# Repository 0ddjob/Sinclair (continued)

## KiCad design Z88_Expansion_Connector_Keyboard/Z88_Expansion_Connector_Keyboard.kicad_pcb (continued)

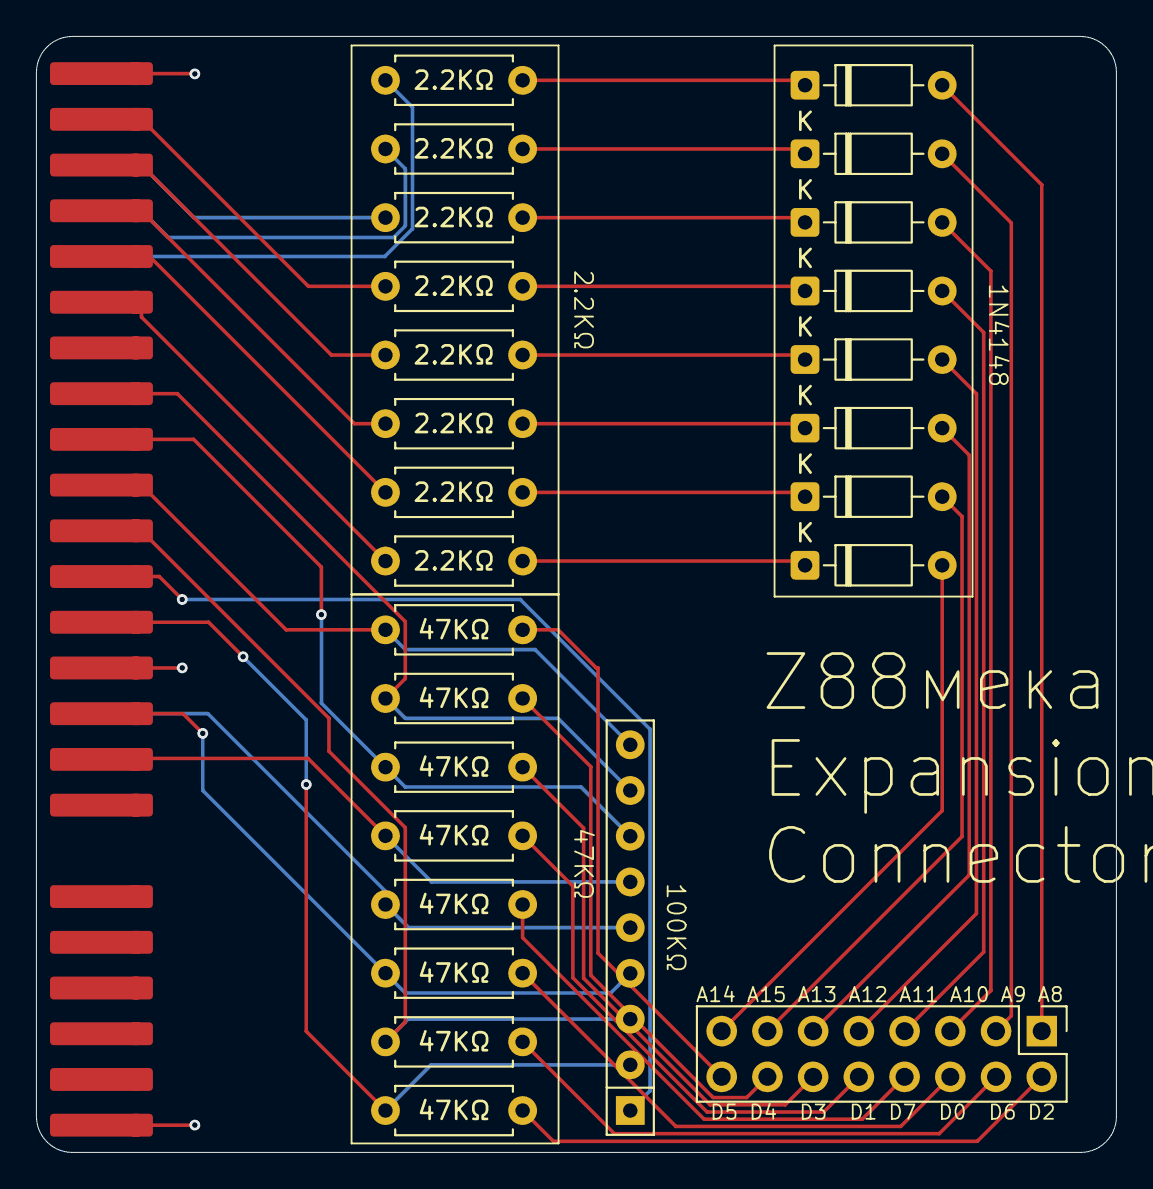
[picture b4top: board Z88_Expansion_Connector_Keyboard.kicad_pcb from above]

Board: 2 copper layers, 60.0 x 62.0 mm, 27 parts (0 on the bottom side), 42 nets.

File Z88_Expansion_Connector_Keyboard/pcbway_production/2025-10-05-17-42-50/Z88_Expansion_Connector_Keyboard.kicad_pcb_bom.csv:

Designator,Quantity,Value,Footprint,Package,MPN,DNP,Mount_Type,Description,Sim.Device,Sim.Pins
"D1, D2, D3, D4, D5, D6, D7, D8",8,1N4148,D_DO-35_SOD27_P7.62mm_Horizontal,,,,tht,"100V 0.15A standard switching diode, DO-35",D,1=K 2=A
J1,1,Z88 Expansion Connector,Z88 Expansion Connector,,,,tht,Z88 Cambridge Computer expansion connector,,
J2,1,From Keyboard,PinHeader_2x08_P2.54mm_Vertical,,,,tht,"Generic connector, double row, 02x08, odd/even pin numbering scheme (row 1 odd numbers, row 2 even numbers), script generated (kicad-library-utils/schlib/autogen/connector/)",,
"R1, R2, R3, R4, R5, R6, R7, R8",8,2.2KΩ,R_Axial_DIN0207_L6.3mm_D2.5mm_P7.62mm_Horizontal,,,,tht,Resistor,,
"R10, R11, R12, R13, R14, R15, R16, R9",8,47KΩ,R_Axial_DIN0207_L6.3mm_D2.5mm_P7.62mm_Horizontal,,,,tht,Resistor,,
RN1,1,100KΩ,R_Array_SIP9,,,,tht,"8 resistor network, star topology, bussed resistors, small symbol",,

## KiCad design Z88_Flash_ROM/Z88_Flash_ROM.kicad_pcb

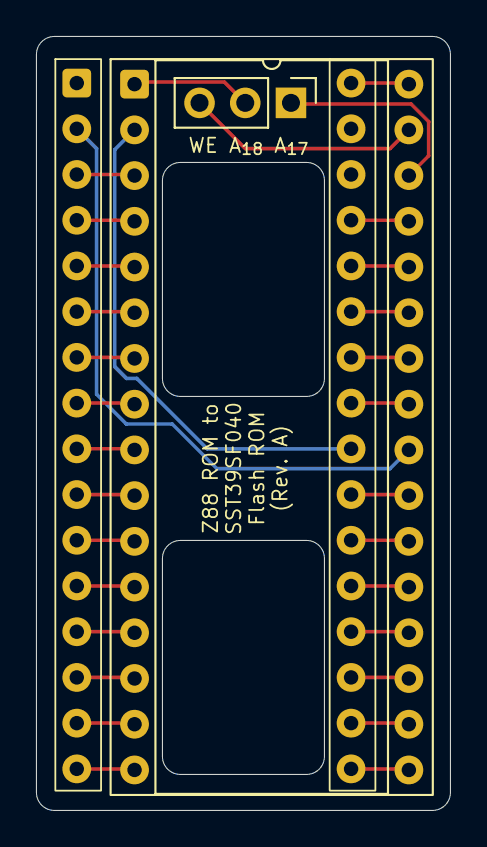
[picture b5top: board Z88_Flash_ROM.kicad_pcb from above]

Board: 2 copper layers, 23.0 x 43.0 mm, 3 parts (0 on the bottom side), 32 nets.

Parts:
J1: Conn_01x03; PinHeader_1x03_P2.54mm_Vertical
U1: SST39SF040; DIP-32_W15.24mm_Socket
U2: Z88_ROM; DIP-32_Adapter

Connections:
+5V: U1.32 (VCC), U2.32 (VCC)
/A_{0}: U1.12 (A0), U2.12 (A_{0})
/A_{1}: U1.11 (A1), U2.11 (A_{1})
/A_{2}: U1.10 (A2), U2.10 (A_{2})
/A_{3}: U1.9 (A3), U2.9 (A_{3})
/A_{4}: U1.8 (A4), U2.8 (A_{4})
/A_{5}: U1.7 (A5), U2.7 (A_{5})
/A_{6}: U1.6 (A6), U2.6 (A_{6})
/A_{7}: U1.5 (A7), U2.5 (A_{7})
/A_{8}: U1.27 (A8), U2.27 (A_{8})
/A_{9}: U1.26 (A9), U2.26 (A_{9})
/A_{10}: U1.23 (A10), U2.23 (A_{10})
/A_{11}: U1.25 (A11), U2.25 (A_{11})
/A_{12}: U1.4 (A12), U2.4 (A_{12})
/A_{13}: U1.28 (A13), U2.28 (A_{13})
/A_{14}: U1.29 (A14), U2.29 (A_{14})
/A_{15}: U1.3 (A15), U2.3 (A_{15})
/A_{16}: U1.2 (A16), U2.24 (A_{16})
/CE: U1.22 (CE), U2.22 (IPCE)
/D_{0}: U1.13 (D0), U2.13 (D_{0})
/D_{1}: U1.14 (D1), U2.14 (D_{1})
/D_{2}: U1.15 (D2), U2.15 (D_{2})
/D_{3}: U1.17 (D3), U2.17 (D_{3})
/D_{4}: U1.18 (D4), U2.18 (D_{4})
/D_{5}: U1.19 (D5), U2.19 (D_{5})
/D_{6}: U1.20 (D6), U2.20 (D_{6})
/D_{7}: U1.21 (D7), U2.21 (D_{7})
/ROE: U1.24 (OE), U2.2 (ROE)
A_{17}: J1.1, U1.30 (A17)
A_{18}: J1.2, U1.1 (A18)
GND: U1.16 (GND), U2.16 (GND)
WE: J1.3, U1.31 (PGM)

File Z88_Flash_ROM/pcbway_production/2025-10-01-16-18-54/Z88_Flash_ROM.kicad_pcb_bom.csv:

Designator,Quantity,Value,Footprint,Package,MPN,DNP,Mount_Type,Description
J1,1,Conn_01x03,PinHeader_1x03_P2.54mm_Vertical,,,,tht,"Generic connector, single row, 01x03, script generated (kicad-library-utils/schlib/autogen/connector/)"
U1,1,SST39SF040,DIP-32_W15.24mm_Socket,,,,tht,Silicon Storage Technology (SSF) 512k x 8 Flash ROM
U2,1,Z88_ROM,DIP-32_Adapter,,,,tht,

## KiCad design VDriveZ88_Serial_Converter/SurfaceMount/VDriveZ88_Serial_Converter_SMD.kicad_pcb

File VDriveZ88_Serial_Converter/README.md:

# VDrive Serial Interface Converter for Z88
Refer to [Ben Vyre's project page](https://benryves.com/products/vdrivez88) and [Github](https://github.com/benryves/VDriveZ88/) for the background.

## RS232 Serial Pinouts
Note that this design uses the Z88's non-standard DE9 RS232 pin numbering.<br>
For [standard RS232 pin numbering](https://cambridgez88.jira.com/wiki/spaces/UG/pages/35913795/Appendix+B+-+Serial+port+and+transfer+protocols):<br>
|Standard DE9|Z88 DE9|
|------------|-------|
| DCD (pin 1) | pin 8         |
| RXD (pin 2) | pin 3         |
| TXD (pin 3) | pin 2         |
| DTR (pin 4) | not connected |
| GND (pin 5) | pin 7         |
| DSR (pin 6) | pin 8         |
| RTS (pin 7) | pin 4         |
| CTS (pin 8) | pin 5         |
| RI  (pin 9) | not connected |

## BOM
- 1 x MAX232
- 1 x 2.2KΩ pullup resistor
- 5 x 1µF ceramic capacitors (2.5mm pitch)
- 1 x 9-way 2.54mm pitch pin header for Z88 serial
- 1 x 8-way 2mm pitch pin header for VDrive interface
- 1 x 2-way 2.54mm pin header for +5VDC power input
- 2 x M2 screws for mounting the PCB

Note that pin headers are optional - you could just directly solder the wires to the PCB.<br>

The centre of each M2 mounting hole is inset 3mm from each edge.<br>

## Status
9-Aug-2025: This design is currently untested

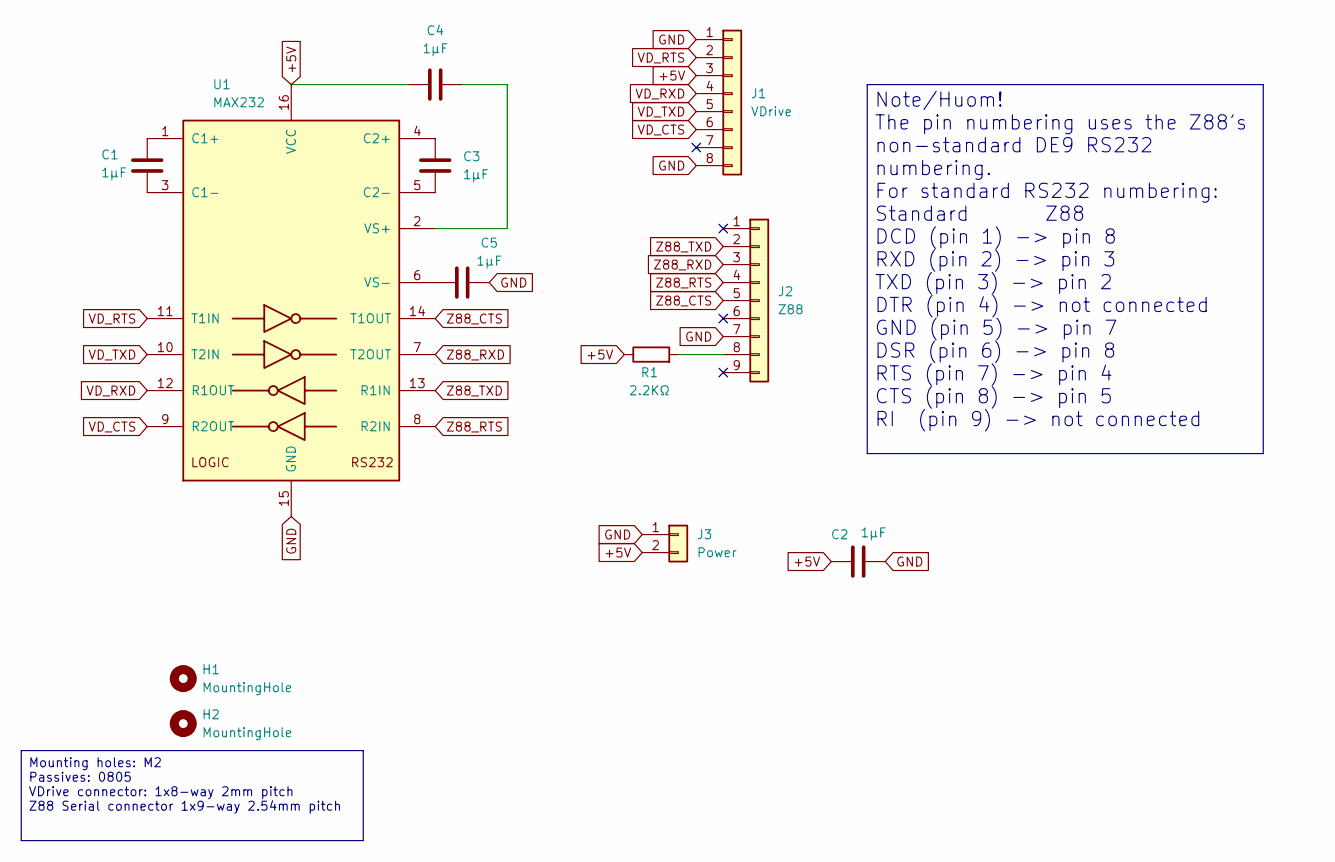
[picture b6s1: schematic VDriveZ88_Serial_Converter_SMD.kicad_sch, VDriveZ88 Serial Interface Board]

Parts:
C1, C2, C3, C4, C5: 1µF; C_0805_2012Metric_Pad1.18x1.45mm_HandSolder
H1, H2: MountingHole; MountingHole_2.2mm_M2
J1: VDrive; PinHeader_1x08_P2.00mm_Vertical
J2: Z88; PinHeader_1x09_P2.54mm_Vertical
J3: Power; PinHeader_1x02_P2.54mm_Vertical
R1: 2.2KΩ; R_0805_2012Metric_Pad1.20x1.40mm_HandSolder
U1: MAX232; SOIC-16W_7.5x10.3mm_P1.27mm

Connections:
+5V: C2.1, C4.1, J1.3, J3.2, R1.1, U1.16 (VCC)
GND: C2.2, C5.2, J1.1, J1.8, J2.7, J3.1, U1.15 (GND)
unnamed: J2.8, R1.2
unnamed: C1.1, U1.1 (C1+)
unnamed: C1.2, U1.3 (C1-)
unnamed: C3.1, U1.4 (C2+)
unnamed: C3.2, U1.5 (C2-)
unnamed: C4.2, U1.2 (VS+)
unnamed: C5.1, U1.6 (VS-)
VD_CTS: J1.6, U1.9 (R2OUT)
VD_RTS: J1.2, U1.11 (T1IN)
VD_RXD: J1.4, U1.12 (R1OUT)
VD_TXD: J1.5, U1.10 (T2IN)
Z88_CTS: J2.5, U1.14 (T1OUT)
Z88_RTS: J2.4, U1.8 (R2IN)
Z88_RXD: J2.3, U1.7 (T2OUT)
Z88_TXD: J2.2, U1.13 (R1IN)

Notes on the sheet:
Mounting holes: M2 Passives: 0805 VDrive connector: 1x8-way 2mm pitch Z88 Serial connector 1x9-way 2.54mm pitch
Note/Huom! The pin numbering uses the Z88's non-standard DE9 RS232 numbering. For standard RS232 numbering: Standard Z88 DCD (pin 1) -> pin 8 RXD (pin 2) -> pin 3 TXD (pin 3) -> pin 2 DTR (pin 4) -> not connected GND (pin 5) -> pin 7 DSR (pin 6) -> pin 8 RTS (pin 7) -> pin 4 CTS (pin 8) -> pin 5 RI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

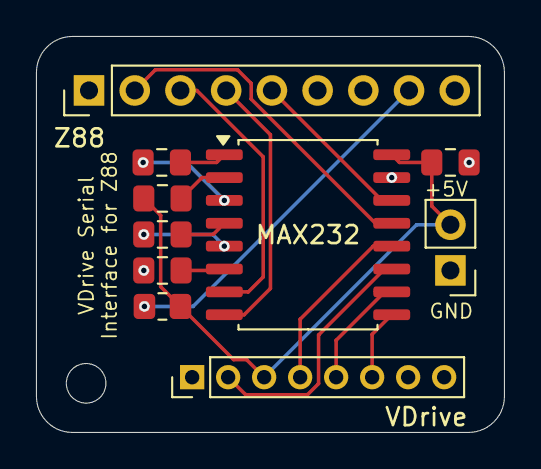
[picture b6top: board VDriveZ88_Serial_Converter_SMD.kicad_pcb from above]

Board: 2 copper layers, 26.0 x 22.0 mm, 11 parts (0 on the bottom side), 17 nets.

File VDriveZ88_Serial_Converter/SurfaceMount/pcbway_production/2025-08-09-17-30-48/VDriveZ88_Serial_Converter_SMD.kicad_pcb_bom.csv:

Designator,Quantity,Value,Footprint,Package,MPN,DNP,Mount_Type,Description
"C1, C2, C3, C4, C5",5,1µF,C_0805_2012Metric_Pad1.18x1.45mm_HandSolder,,,,smt,Unpolarized capacitor
J1,1,VDrive,PinHeader_1x08_P2.00mm_Vertical,,,,tht,"Generic connector, single row, 01x08, script generated (kicad-library-utils/schlib/autogen/connector/)"
J2,1,Z88,PinHeader_1x09_P2.54mm_Vertical,,,,tht,"Generic connector, single row, 01x09, script generated (kicad-library-utils/schlib/autogen/connector/)"
J3,1,Power,PinHeader_1x02_P2.54mm_Vertical,,,,tht,"Generic connector, single row, 01x02, script generated (kicad-library-utils/schlib/autogen/connector/)"
R1,1,2.2KΩ,R_0805_2012Metric_Pad1.20x1.40mm_HandSolder,,,,smt,Resistor
U1,1,MAX232,SOIC-16W_7.5x10.3mm_P1.27mm,,,,smt,"Dual RS232 driver/receiver, 5V supply, 120kb/s, 0C-70C"

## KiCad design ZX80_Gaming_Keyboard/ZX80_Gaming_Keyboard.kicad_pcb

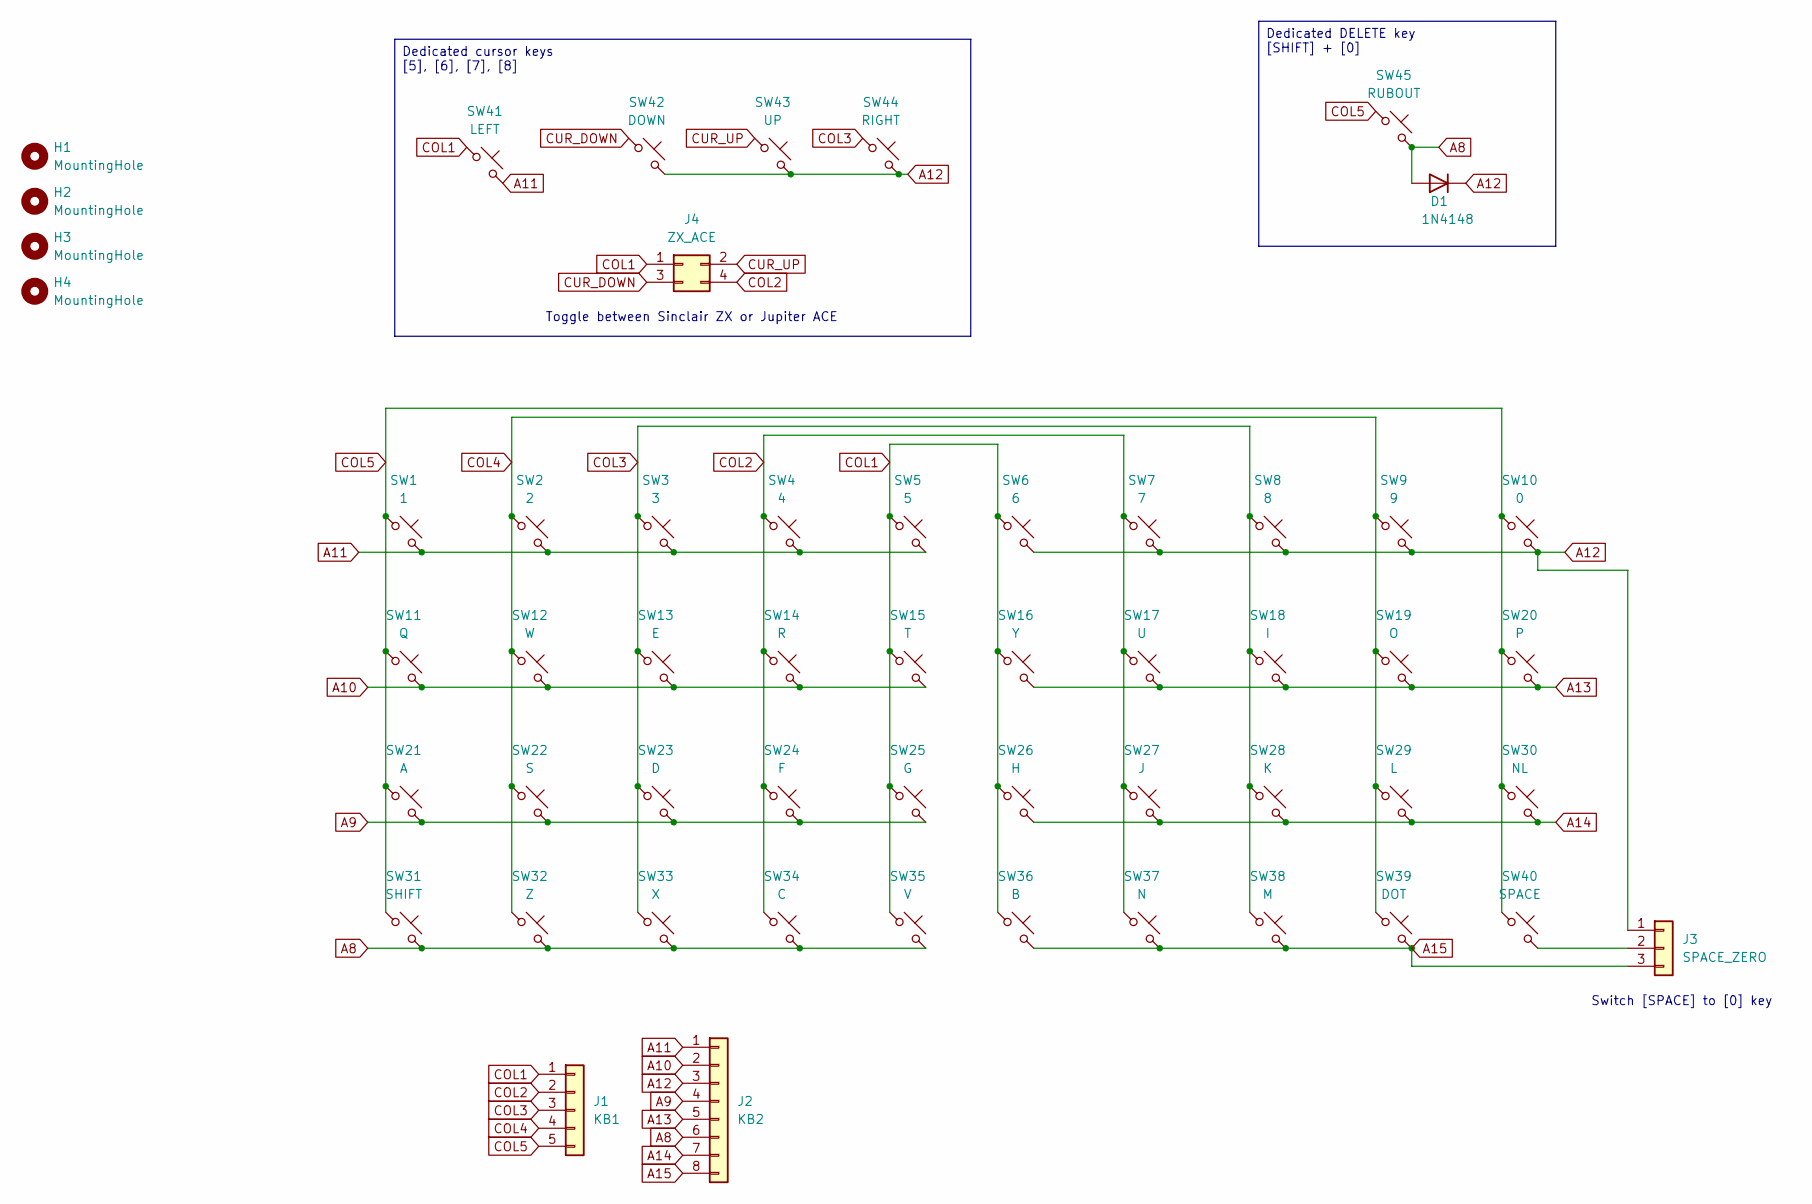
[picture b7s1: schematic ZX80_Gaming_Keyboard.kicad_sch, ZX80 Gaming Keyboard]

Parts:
D1: 1N4148; D_DO-35_SOD27_P7.62mm_Horizontal
H1, H2, H3, H4: MountingHole; MountingHole_3.2mm_M3
J1: KB1; PinHeader_1x05_P2.54mm_Vertical
J2: KB2; PinHeader_1x08_P2.54mm_Vertical
J3: SPACE_ZERO; PinHeader_1x03_P2.54mm_Vertical
J4: ZX_ACE; PinHeader_2x02_P2.54mm_Vertical
SW1: 1; SW_Cherry_MX_1.00u_PCB
SW2: 2; SW_Cherry_MX_1.00u_PCB
SW3: 3; SW_Cherry_MX_1.00u_PCB
SW4: 4; SW_Cherry_MX_1.00u_PCB
SW5: 5; SW_Cherry_MX_1.00u_PCB
SW6: 6; SW_Cherry_MX_1.00u_PCB
SW7: 7; SW_Cherry_MX_1.00u_PCB
SW8: 8; SW_Cherry_MX_1.00u_PCB
SW9: 9; SW_Cherry_MX_1.00u_PCB
SW10: 0; SW_Cherry_MX_1.00u_PCB
SW11: Q; SW_Cherry_MX_1.00u_PCB
SW12: W; SW_Cherry_MX_1.00u_PCB
SW13: E; SW_Cherry_MX_1.00u_PCB
SW14: R; SW_Cherry_MX_1.00u_PCB
SW15: T; SW_Cherry_MX_1.00u_PCB
SW16: Y; SW_Cherry_MX_1.00u_PCB
SW17: U; SW_Cherry_MX_1.00u_PCB
SW18: I; SW_Cherry_MX_1.00u_PCB
SW19: O; SW_Cherry_MX_1.00u_PCB
SW20: P; SW_Cherry_MX_1.00u_PCB
SW21: A; SW_Cherry_MX_1.00u_PCB
SW22: S; SW_Cherry_MX_1.00u_PCB
SW23: D; SW_Cherry_MX_1.00u_PCB
SW24: F; SW_Cherry_MX_1.00u_PCB
SW25: G; SW_Cherry_MX_1.00u_PCB
SW26: H; SW_Cherry_MX_1.00u_PCB
SW27: J; SW_Cherry_MX_1.00u_PCB
SW28: K; SW_Cherry_MX_1.00u_PCB
SW29: L; SW_Cherry_MX_1.00u_PCB
SW30: NL; SW_Cherry_MX_1.00u_PCB
SW31: SHIFT; SW_Cherry_MX_1.00u_PCB
SW32: Z; SW_Cherry_MX_1.00u_PCB
SW33: X; SW_Cherry_MX_1.00u_PCB
SW34: C; SW_Cherry_MX_1.00u_PCB
SW35: V; SW_Cherry_MX_1.00u_PCB
SW36: B; SW_Cherry_MX_1.00u_PCB
SW37: N; SW_Cherry_MX_1.00u_PCB
SW38: M; SW_Cherry_MX_1.00u_PCB
SW39: DOT; SW_Cherry_MX_1.00u_PCB
SW40: SPACE; SW_Cherry_MX_1.00u_PCB
SW41: LEFT; SW_Cherry_MX_1.00u_PCB
SW42: DOWN; SW_Cherry_MX_1.00u_PCB
SW43: UP; SW_Cherry_MX_1.00u_PCB
SW44: RIGHT; SW_Cherry_MX_1.00u_PCB
SW45: RUBOUT; SW_Cherry_MX_1.00u_PCB

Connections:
A8: D1.2 (A), J2.6, SW31.2, SW32.2, SW33.2, SW34.2, SW35.2, SW45.2
A9: J2.4, SW21.2, SW22.2, SW23.2, SW24.2, SW25.2
A10: J2.2, SW11.2, SW12.2, SW13.2, SW14.2, SW15.2
A11: J2.1, SW1.2, SW2.2, SW3.2, SW4.2, SW5.2, SW41.2
A12: D1.1 (K), J2.3, J3.1, SW6.2, SW7.2, SW8.2, SW9.2, SW10.2, SW42.2, SW43.2, SW44.2
A13: J2.5, SW16.2, SW17.2, SW18.2, SW19.2, SW20.2
A14: J2.7, SW26.2, SW27.2, SW28.2, SW29.2, SW30.2
A15: J2.8, J3.3, SW36.2, SW37.2, SW38.2, SW39.2
COL1: J1.1, J4.1, SW5.1, SW6.1, SW15.1, SW16.1, SW25.1, SW26.1, SW35.1, SW36.1, SW41.1
COL2: J1.2, J4.4, SW4.1, SW7.1, SW14.1, SW17.1, SW24.1, SW27.1, SW34.1, SW37.1
COL3: J1.3, SW3.1, SW8.1, SW13.1, SW18.1, SW23.1, SW28.1, SW33.1, SW38.1, SW44.1
COL4: J1.4, SW2.1, SW9.1, SW12.1, SW19.1, SW22.1, SW29.1, SW32.1, SW39.1
COL5: J1.5, SW1.1, SW10.1, SW11.1, SW20.1, SW21.1, SW30.1, SW31.1, SW40.1, SW45.1
CUR_DOWN: J4.3, SW42.1
CUR_UP: J4.2, SW43.1
unnamed: J3.2, SW40.2

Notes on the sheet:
Toggle between Sinclair ZX or Jupiter ACE
Switch [SPACE] to [0] key
Dedicated DELETE key [SHIFT] + [0]
Dedicated cursor keys [5], [6], [7], [8]

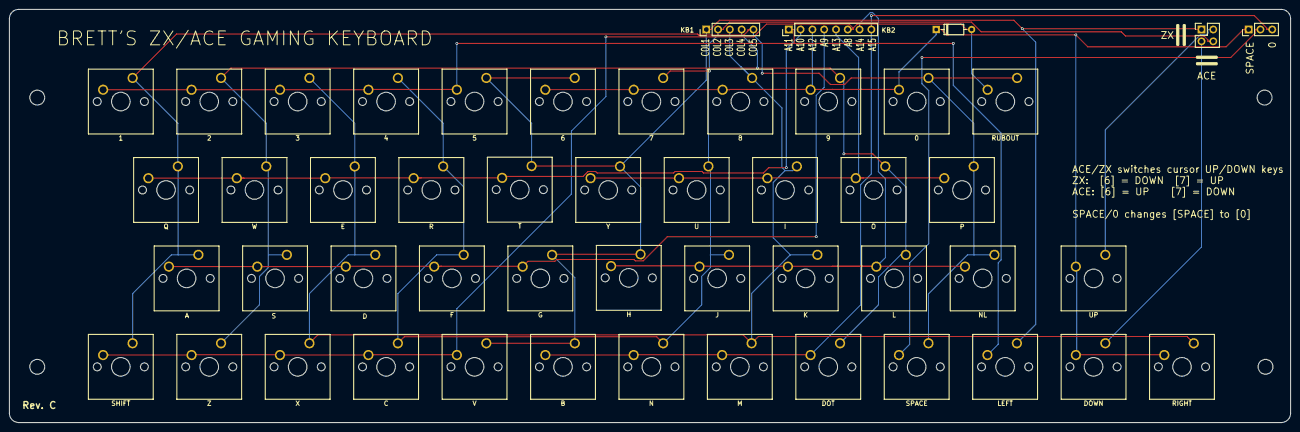
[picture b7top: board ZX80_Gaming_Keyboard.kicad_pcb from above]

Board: 2 copper layers, 276.0 x 89.0 mm, 54 parts (0 on the bottom side), 16 nets.

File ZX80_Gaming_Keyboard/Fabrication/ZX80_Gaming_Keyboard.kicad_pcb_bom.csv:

Designator,Quantity,Value,Footprint,Package,MPN,DNP,Mount_Type,Description,Sim.Device,Sim.Pins
"D1, D2",2,1N4148,D_DO-35_SOD27_P7.62mm_Horizontal,,,,tht,Diode,D,1=K 2=A
J1,1,KB1,PinHeader_1x05_P2.54mm_Vertical,,,,tht,"Generic connector, single row, 01x05, script generated (kicad-library-utils/schlib/autogen/connector/)",,
J2,1,KB2,PinHeader_1x08_P2.54mm_Vertical,,,,tht,"Generic connector, single row, 01x08, script generated (kicad-library-utils/schlib/autogen/connector/)",,
J3,1,SPACE_ZERO,PinHeader_1x03_P2.54mm_Vertical,,,,tht,"Generic connector, single row, 01x03, script generated (kicad-library-utils/schlib/autogen/connector/)",,
J4,1,ZX_ACE,PinHeader_2x02_P2.54mm_Vertical,,,,tht,"Generic connector, double row, 02x02, odd/even pin numbering scheme (row 1 odd numbers, row 2 even numbers), script generated (kicad-library-utils/schlib/autogen/connector/)",,
SW1,1,1,SW_Cherry_MX_1.00u_PCB,,,,tht,"Push button switch, normally open, two pins, 45° tilted",,
SW10,1,0,SW_Cherry_MX_1.00u_PCB,,,,tht,"Push button switch, normally open, two pins, 45° tilted",,
SW11,1,Q,SW_Cherry_MX_1.00u_PCB,,,,tht,"Push button switch, normally open, two pins, 45° tilted",,
SW12,1,W,SW_Cherry_MX_1.00u_PCB,,,,tht,"Push button switch, normally open, two pins, 45° tilted",,
SW13,1,E,SW_Cherry_MX_1.00u_PCB,,,,tht,"Push button switch, normally open, two pins, 45° tilted",,
SW14,1,R,SW_Cherry_MX_1.00u_PCB,,,,tht,"Push button switch, normally open, two pins, 45° tilted",,
SW15,1,T,SW_Cherry_MX_1.00u_PCB,,,,tht,"Push button switch, normally open, two pins, 45° tilted",,
SW16,1,Y,SW_Cherry_MX_1.00u_PCB,,,,tht,"Push button switch, normally open, two pins, 45° tilted",,
SW17,1,U,SW_Cherry_MX_1.00u_PCB,,,,tht,"Push button switch, normally open, two pins, 45° tilted",,
SW18,1,I,SW_Cherry_MX_1.00u_PCB,,,,tht,"Push button switch, normally open, two pins, 45° tilted",,
SW19,1,O,SW_Cherry_MX_1.00u_PCB,,,,tht,"Push button switch, normally open, two pins, 45° tilted",,
SW2,1,2,SW_Cherry_MX_1.00u_PCB,,,,tht,"Push button switch, normally open, two pins, 45° tilted",,
SW20,1,P,SW_Cherry_MX_1.00u_PCB,,,,tht,"Push button switch, normally open, two pins, 45° tilted",,
SW21,1,A,SW_Cherry_MX_1.00u_PCB,,,,tht,"Push button switch, normally open, two pins, 45° tilted",,
SW22,1,S,SW_Cherry_MX_1.00u_PCB,,,,tht,"Push button switch, normally open, two pins, 45° tilted",,
SW23,1,D,SW_Cherry_MX_1.00u_PCB,,,,tht,"Push button switch, normally open, two pins, 45° tilted",,
SW24,1,F,SW_Cherry_MX_1.00u_PCB,,,,tht,"Push button switch, normally open, two pins, 45° tilted",,
SW25,1,G,SW_Cherry_MX_1.00u_PCB,,,,tht,"Push button switch, normally open, two pins, 45° tilted",,
SW26,1,H,SW_Cherry_MX_1.00u_PCB,,,,tht,"Push button switch, normally open, two pins, 45° tilted",,
SW27,1,J,SW_Cherry_MX_1.00u_PCB,,,,tht,"Push button switch, normally open, two pins, 45° tilted",,
SW28,1,K,SW_Cherry_MX_1.00u_PCB,,,,tht,"Push button switch, normally open, two pins, 45° tilted",,
SW29,1,L,SW_Cherry_MX_1.00u_PCB,,,,tht,"Push button switch, normally open, two pins, 45° tilted",,
SW3,1,3,SW_Cherry_MX_1.00u_PCB,,,,tht,"Push button switch, normally open, two pins, 45° tilted",,
SW30,1,NL,SW_Cherry_MX_1.00u_PCB,,,,tht,"Push button switch, normally open, two pins, 45° tilted",,
SW31,1,SHIFT,SW_Cherry_MX_1.00u_PCB,,,,tht,"Push button switch, normally open, two pins, 45° tilted",,
SW32,1,Z,SW_Cherry_MX_1.00u_PCB,,,,tht,"Push button switch, normally open, two pins, 45° tilted",,
SW33,1,X,SW_Cherry_MX_1.00u_PCB,,,,tht,"Push button switch, normally open, two pins, 45° tilted",,
SW34,1,C,SW_Cherry_MX_1.00u_PCB,,,,tht,"Push button switch, normally open, two pins, 45° tilted",,
SW35,1,V,SW_Cherry_MX_1.00u_PCB,,,,tht,"Push button switch, normally open, two pins, 45° tilted",,
SW36,1,B,SW_Cherry_MX_1.00u_PCB,,,,tht,"Push button switch, normally open, two pins, 45° tilted",,
SW37,1,N,SW_Cherry_MX_1.00u_PCB,,,,tht,"Push button switch, normally open, two pins, 45° tilted",,
SW38,1,M,SW_Cherry_MX_1.00u_PCB,,,,tht,"Push button switch, normally open, two pins, 45° tilted",,
SW39,1,DOT,SW_Cherry_MX_1.00u_PCB,,,,tht,"Push button switch, normally open, two pins, 45° tilted",,
SW4,1,4,SW_Cherry_MX_1.00u_PCB,,,,tht,"Push button switch, normally open, two pins, 45° tilted",,
SW40,1,SPACE,SW_Cherry_MX_1.00u_PCB,,,,tht,"Push button switch, normally open, two pins, 45° tilted",,
SW41,1,LEFT,SW_Cherry_MX_1.00u_PCB,,,,tht,"Push button switch, normally open, two pins, 45° tilted",,
SW42,1,DOWN,SW_Cherry_MX_1.00u_PCB,,,,tht,"Push button switch, normally open, two pins, 45° tilted",,
SW43,1,UP,SW_Cherry_MX_1.00u_PCB,,,,tht,"Push button switch, normally open, two pins, 45° tilted",,
SW44,1,RIGHT,SW_Cherry_MX_1.00u_PCB,,,,tht,"Push button switch, normally open, two pins, 45° tilted",,
SW45,1,RUBOUT,SW_Cherry_MX_1.00u_PCB,,,,tht,"Push button switch, normally open, two pins, 45° tilted",,
SW5,1,5,SW_Cherry_MX_1.00u_PCB,,,,tht,"Push button switch, normally open, two pins, 45° tilted",,
SW6,1,6,SW_Cherry_MX_1.00u_PCB,,,,tht,"Push button switch, normally open, two pins, 45° tilted",,
SW7,1,7,SW_Cherry_MX_1.00u_PCB,,,,tht,"Push button switch, normally open, two pins, 45° tilted",,
SW8,1,8,SW_Cherry_MX_1.00u_PCB,,,,tht,"Push button switch, normally open, two pins, 45° tilted",,
SW9,1,9,SW_Cherry_MX_1.00u_PCB,,,,tht,"Push button switch, normally open, two pins, 45° tilted",,

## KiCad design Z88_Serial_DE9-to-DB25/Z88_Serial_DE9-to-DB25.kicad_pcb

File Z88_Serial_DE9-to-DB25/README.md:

# Z88 Serial Port Converter
The Cambridge Computers Z88 has a DE9 serial port with the following [pinout](https://cambridgez88.jira.com/wiki/spaces/UG40/pages/14024777/Appendix+B+-+Serial+port):

|DE9 Pin|Signal|Purpose|DB25 Pin|
|-------|------|-------|--------|
|1|+5V|do not use|n/c|
|2|TxD|transmitted data|2|
|3|RxD|received data|3|
|4|RTS|request to send|4|
|5|CTS|clear to send|5|
|6|unknown| do not use|n/c|
|7|GND|signal ground|7|
|8|DCD|data carrier detect|6 & 8|
|9|DTR|data terminal ready|20|

To connect to a device with a DB25 plug we need to through-connect the DE9 pins to the equivalent on the DB25 side.  Additionally, we need to connect DB25 pin 6 (DSR, data set ready) to the DCD signal.<br>

Note that DB25 pin 1 is Protective Ground (PG) and must not be connected to signal ground.<br>

Z88 side: DE9 male<br>
DB25 side: DB25 female<br>

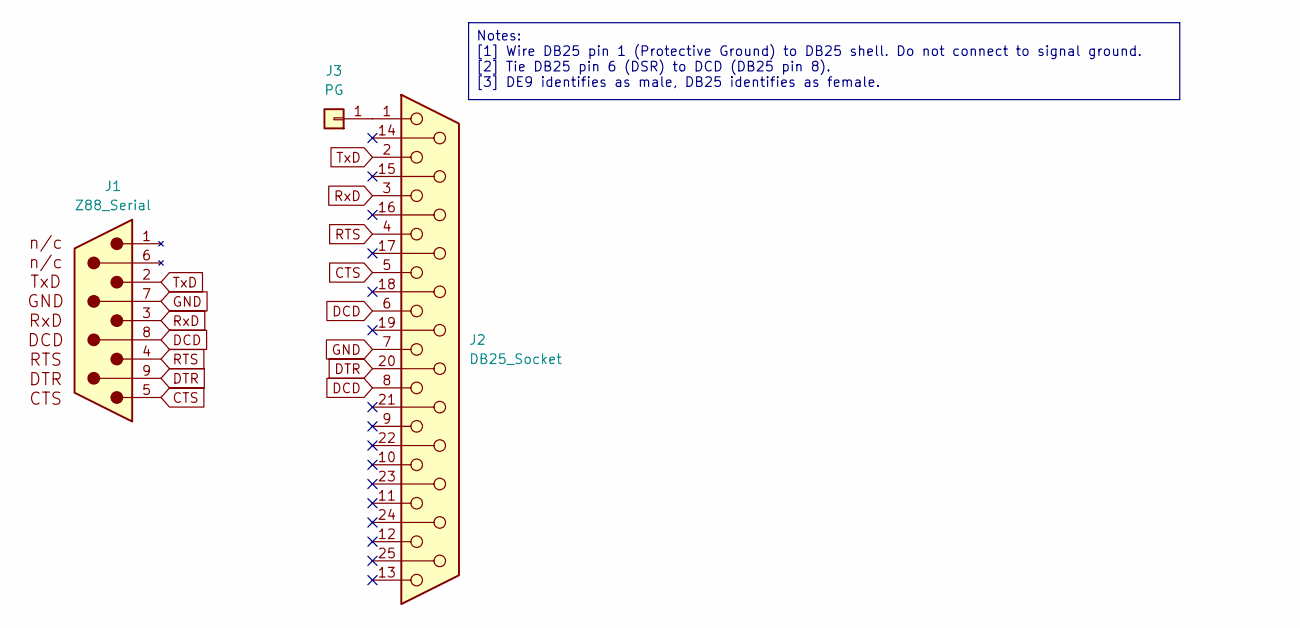
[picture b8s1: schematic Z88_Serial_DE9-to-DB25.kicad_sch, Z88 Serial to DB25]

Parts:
J1: Z88_Serial; DSUB-9_Pins_EdgeMount_P2.77mm
J2: DB25_Socket; DSUB-25_Socket_EdgeMount_P2.77mm
J3: PG; PinHeader_1x01_P2.54mm_Vertical

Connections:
CTS: J1.5, J2.5
DCD: J1.8, J2.6, J2.8
DTR: J1.9, J2.20
GND: J1.7, J2.7
unnamed: J2.1, J3.1
RTS: J1.4, J2.4
RxD: J1.3, J2.3
TxD: J1.2, J2.2

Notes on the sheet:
Notes: [1] Wire DB25 pin 1 (Protective Ground) to DB25 shell. Do not connect to signal ground. [2] Tie DB25 pin 6 (DSR) to DCD (DB25 pin 8). [3] DE9 identifies as male, DB25 identifies as female.

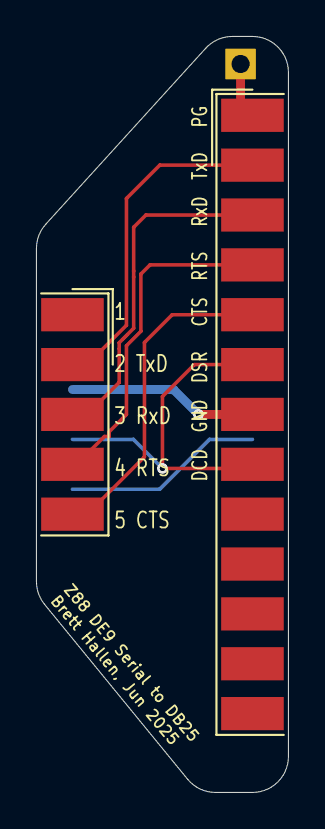
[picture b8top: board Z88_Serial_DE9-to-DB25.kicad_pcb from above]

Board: 2 copper layers, 14.0 x 42.0 mm, 3 parts (0 on the bottom side), 8 nets.

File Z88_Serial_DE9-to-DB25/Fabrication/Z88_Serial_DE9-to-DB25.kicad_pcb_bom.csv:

Designator,Quantity,Value,Footprint,Package,MPN,DNP,Mount_Type,Description
J1,1,Z88_Serial,DSUB-9_Pins_EdgeMount_P2.77mm,,,,smt,
J2,1,DB25_Socket,DSUB-25_Socket_EdgeMount_P2.77mm,,,,smt,"25-pin D-SUB connector, socket (female)"
J3,1,PG,PinHeader_1x01_P2.54mm_Vertical,,,,tht,"Generic connector, single row, 01x01, script generated (kicad-library-utils/schlib/autogen/connector/)"

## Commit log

2025-05-21 Reorganising Sinclair related projects
2025-05-21 Moved ZX81 project to Sinclair folder
2025-05-21 Finalised keyboard design for testing
2025-05-21 Cosmetic changes to documentation
2025-05-24 Modified PCB layout after testing initial layout
2025-05-24 Added BOM to schematic
2025-06-15 Revised PCB layout correcting errors
2025-06-15 Revised ZX/ACE switch
2025-06-15 Renamed schematic file
2025-06-19 Initial Z88 serial converter design
2025-06-27 Initial Rev. C changes
2025-06-27 Added standard DE9 serial details
2025-06-27 Added images of built keyboards
2025-07-01 Progress commit
2025-07-01 Added schematics
2025-07-01 Added 3D models
2025-07-02 Datasheet for connector
2025-07-03 Keyboard layout changes
2025-07-03 6.25u & 7u SPACE bar lengths
2025-07-04 Added T-cursor layout
2025-07-04 Modified T-cursor layout
2025-07-04 Swapped DOWN/RIGHT cursors (thanks Alex Q)
2025-07-04 Routing completed
2025-07-07 Final tweaks before test fabrication
2025-07-25 Archiving Rev. A design
2025-07-25 Started Rev. B design
2025-07-26 Swapped CAPS LOCK & DIAMOND
2025-07-31 Finalised Rev. B design
2025-08-09 Added note to schematic about Z88 port
2025-08-09 Updated schematic notes
2025-08-09 Changed VDrive connector to 2mm pitch
2025-08-09 Added surface mount version
2025-08-16 Updated ISO Rev. B, removed obsolete designs
2025-10-01 Initial design
2025-10-01 Reduced PCB thickness
2025-10-05 ANSI keyboard design
2025-10-05 Updated ISO layout keyboard
2025-10-06 Cosmetic changes
